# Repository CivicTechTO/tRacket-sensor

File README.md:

# tRacket: Community-Driven Urban Noise Monitoring

This repository contains all source code and hardware design files for the [tRacket](https://tracket.info/) noise sensor.

## Overview

Environmental noise, especially in urban settings, is a [known public health concern](https://www.toronto.ca/wp-content/uploads/2017/11/8f98-tph-How-Loud-is-Too-Loud-Health-Impacts-Environmental-Noise.pdf):

> The growing body of evidence indicates that exposure to excessive environmental
noise does not only impact quality of life and cause hearing loss but also has other health impacts, such as cardiovascular effects, cognitive impacts, sleep disturbance and mental health effects.

The tRacket noise sensor continuous monitors ambient sound levels (in [decibels](https://en.wikipedia.org/wiki/Decibel), dBA) and sends these measurements to an [online dashboard](https://dashboard.tracket.info/locations) ([also on GitHub](https://github.com/CivicTechTO/tRacket-dashboard)). Our goal is to help local communities better understand the sound levels and extreme noise events that they experience day to day.

The project has been started and is maintained by volunteers from the [CivicTech Toronto](http://www.civictech.ca) community.

## Privacy

We followed Privacy by Design principles in setting up the data collection. 

1. The sound meter devices are deployed on private properties in residential areas at different locations in the city. We are **not publishing exact device locations**. 
2. The devices **do not record sound** only sound levels in A-weighted decibel levels (dBA)(https://en.wikipedia.org/wiki/Decibel). 
3. We calculate minimum and maximum sound levels at 5 minute intervals on the device and **only broadcast these aggregate values** (along wiht the device ID) to a database.

## Source Code

The [noisemeter-device](/noisemeter-device) folder contains the device's source code, which is written in C++ and can be built using [PlatformIO](https://platformio.org/). Build instructions are available [in the online documentation](https://civictechto.github.io/tRacket-sensor/md_noisemeter_device_BUILD.html).

The source code is released under the [GNU GPL v3 license](/noisemeter-device/LICENSE).

## Hardware Files

The [hardware](/hardware) folder contains design files and documentation for each iteration of the sensor hardware. The PCBs are designed using [KiCAD](https://www.kicad.org/).

The hardware design files are released under an [open hardware license](/hardware/pcb-rev2/LICENSE).

## For Developers

* Check out the [Issues page](https://github.com/CivicTechTO/tRacket-sensor/issues) to see current bugs and feature requests. Any contributions are welcome!
* Online documentation of the firmware [is available here](https://civictechto.github.io/tRacket-sensor/).

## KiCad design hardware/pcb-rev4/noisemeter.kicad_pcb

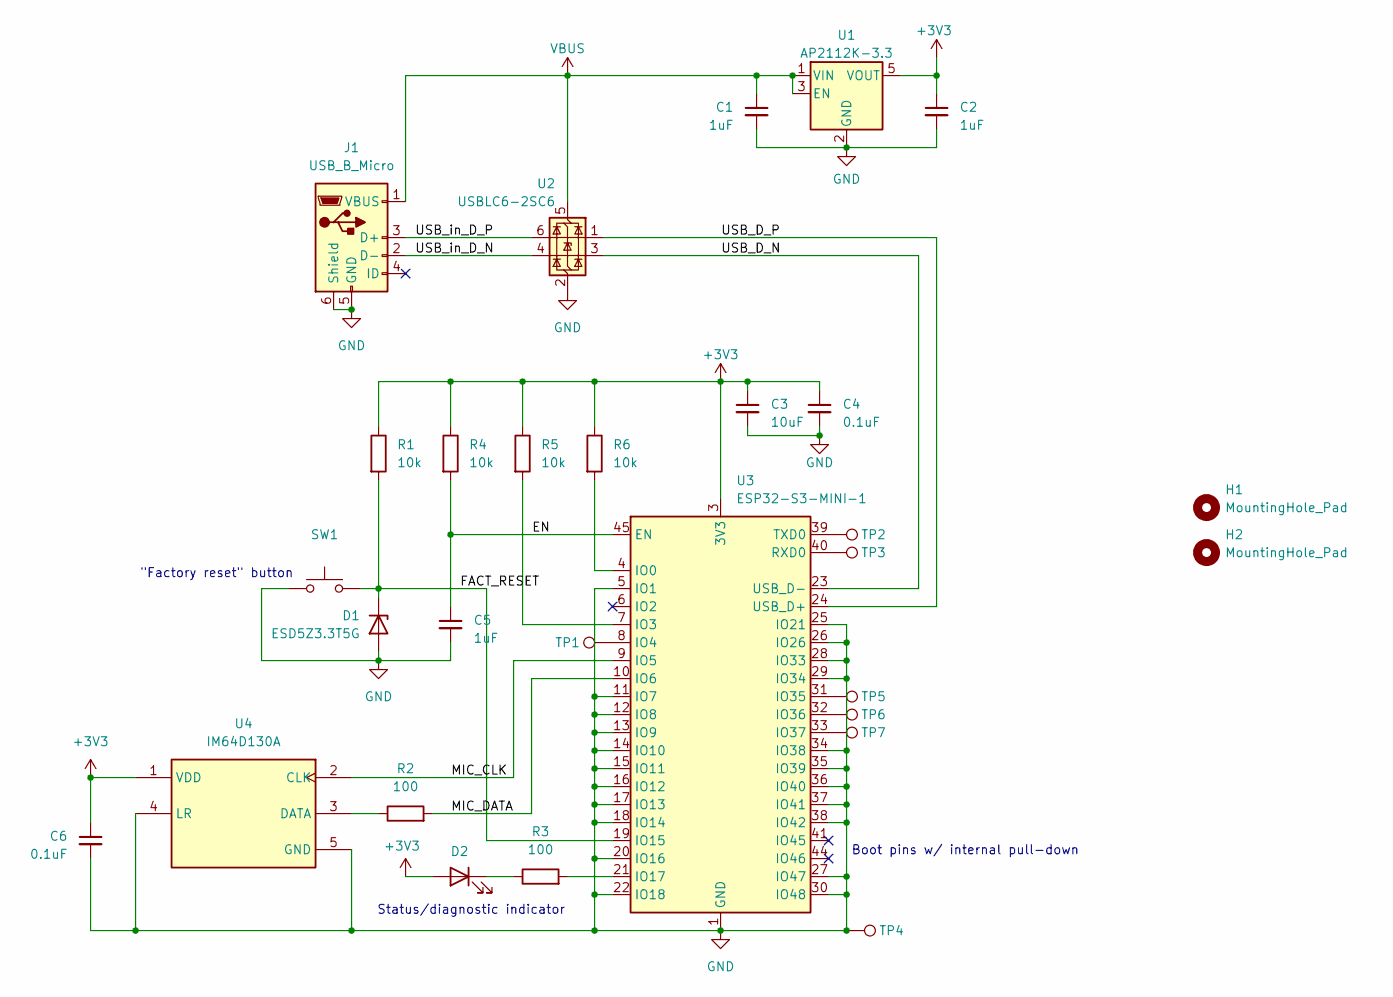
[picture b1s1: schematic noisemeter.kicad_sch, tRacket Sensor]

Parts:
C1, C2, C5: 1uF; C_0603_1608Metric; Part Number CC0603KRX7R7BB105
C3: 10uF; C_0805_2012Metric; Part Number CL21A106KOQNNNE
C4, C6: 0.1uF; C_0603_1608Metric; Part Number CC0603KRX7R6BB104
D1: ESD5Z3.3T5G; D_0603_1608Metric; Part Number ESD5Z3.3T5G
D2: LED; LED_0603_1608Metric; Part Number APT1608LVBC/D
H1, H2: MountingHole_Pad; MountingHole_2.5mm
J1: USB_B_Micro; USB_Micro-B_Molex_47346-0001; Part Number 0473460001
R1, R4, R5, R6: 10k; R_0603_1608Metric
R2, R3: 100; R_0603_1608Metric
SW1: SW_Push; SW_SPST_EVQP7C; Part Number EVQ-P7C01P
TP1, TP2, TP3, TP4, TP5, TP6, TP7: TestPoint; TestPoint_Pad_D1.0mm
U1: AP2112K-3.3; SOT-23-5; Part Number AP2112K-3.3TRG1
U2: USBLC6-2SC6; SOT-23-6; Part Number USBLC6-2SC6
U3: ESP32-S3-MINI-1; ESP32-S2-MINI-1; Part Number ESP32-S3-MINI-1-N8
U4: IM64D130A; IFX-PG-TLGA-5-6-V; Part Number IM64D130AXTMA1

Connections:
+3V3: C2.1, C3.1, C4.1, C6.1, D2.2 (A), R1.1, R4.1, R5.1, R6.1, U1.5 (VOUT), U3.3 (3V3), U4.1 (VDD)
/EN: C5.1, R4.2, U3.45 (EN)
/FACT_RESET: D1.1 (K), R1.2, SW1.1, U3.19 (IO15)
/MIC_CLK: U3.9 (IO5), U4.2 (CLK)
/MIC_DATA: R2.2, U3.10 (IO6)
/USB_D_N: U2.3 (I/O2), U3.23 (USB_D-)
/USB_D_P: U2.1 (I/O1), U3.24 (USB_D+)
/USB_in_D_N: J1.2 (D-), U2.4 (I/O2)
/USB_in_D_P: J1.3 (D+), U2.6 (I/O1)
GND: C1.2, C2.2, C3.2, C4.2, C5.2, C6.2, D1.2 (A), J1.5 (GND), J1.6 (Shield), SW1.2, TP4.1, U1.2 (GND), U2.2 (GND), U3.1 (GND), U3.2 (GND), U3.5 (IO1), U3.11 (IO7), U3.12 (IO8), U3.13 (IO9), U3.14 (IO10), U3.15 (IO11), U3.16 (IO12), U3.17 (IO13), U3.18 (IO14), U3.20 (IO16), U3.22 (IO18), U3.25 (IO21), U3.26 (IO26), U3.27 (IO47), U3.28 (IO33), U3.29 (IO34), U3.30 (IO48), U3.34 (IO38), U3.35 (IO39), U3.36 (IO40), U3.37 (IO41), U3.38 (IO42), U3.42 (GND), U3.43 (GND), U3.46 (GND), U3.47 (GND), U3.48 (GND), U3.49 (GND), U3.50 (GND), U3.51 (GND), U3.52 (GND), U3.53 (GND), U3.54 (GND), U3.55 (GND), U3.56 (GND), U3.57 (GND), U3.58 (GND), U3.59 (GND), U3.60 (GND), U3.61 (GND), U3.62 (GND), U3.63 (GND), U3.64 (GND), U3.65 (GND), U4.4 (LR), U4.5 (GND)
unnamed: D2.1 (K), R3.1
unnamed: R6.2, U3.4 (IO0)
unnamed: R5.2, U3.7 (IO3)
unnamed: TP1.1, U3.8 (IO4)
unnamed: R3.2, U3.21 (IO17)
unnamed: TP5.1, U3.31 (IO35)
unnamed: TP6.1, U3.32 (IO36)
unnamed: TP7.1, U3.33 (IO37)
unnamed: TP3.1, U3.40 (RXD0)
unnamed: TP2.1, U3.39 (TXD0)
unnamed: R2.1, U4.3 (DATA)
VBUS: C1.1, J1.1 (VBUS), U1.1 (VIN), U1.3 (EN), U2.5 (VBUS)

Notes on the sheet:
Status/diagnostic indicator
Boot pins w/ internal pull-down
"Factory reset" button

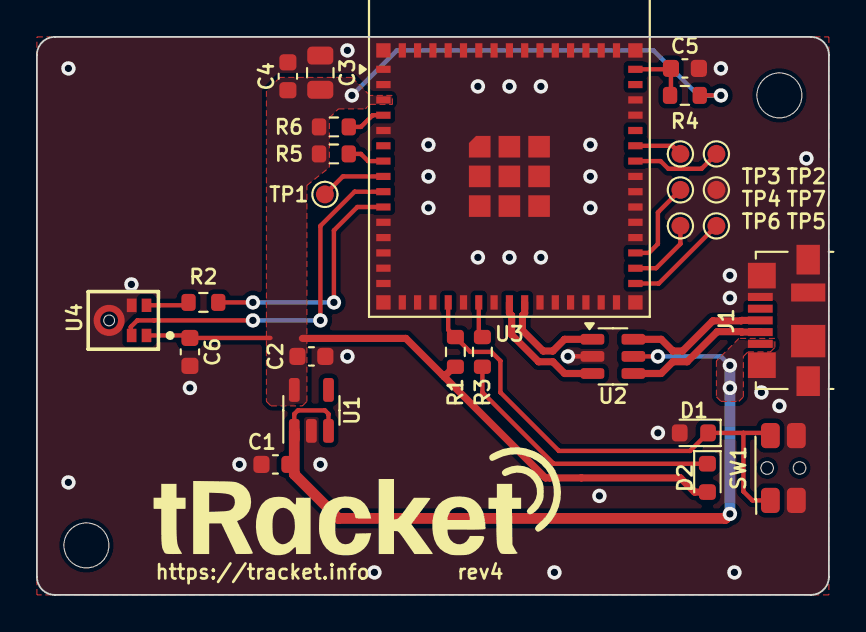
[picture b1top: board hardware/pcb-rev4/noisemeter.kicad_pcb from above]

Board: 2 copper layers, 44.0 x 31.0 mm, 29 parts (0 on the bottom side), 22 nets.

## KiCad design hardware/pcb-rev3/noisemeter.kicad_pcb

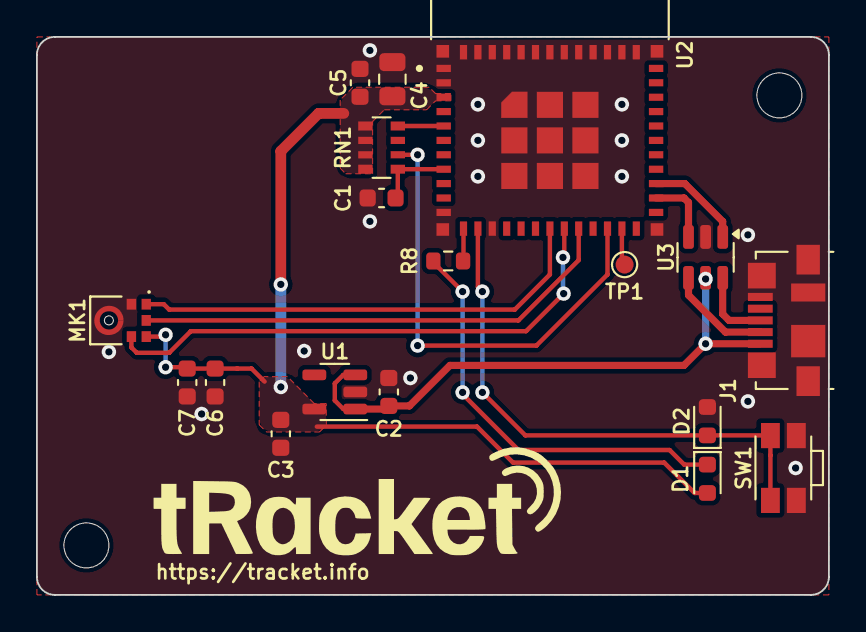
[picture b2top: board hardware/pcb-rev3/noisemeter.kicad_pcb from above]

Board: 2 copper layers, 44.0 x 31.0 mm, 20 parts (0 on the bottom side), 17 nets.

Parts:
C1, C2, C3: 1uF; C_0603_1608Metric
C4: 10uF; C_0805_2012Metric
C5, C6: 0.1uF; C_0603_1608Metric
C7: 200pF; C_0603_1608Metric
D1: LED; LED_0603_1608Metric
D2: ESD5Z3.3T5G; D_0603_1608Metric
H1, H2: MountingHole_Pad; MountingHole_2.5mm
J1: USB_B_Micro; USB_Micro-B_Molex_47346-0001
MK1: SPH0645LM4H-B; MIC_SPH0645LM4H-B
R8: 51; R_0603_1608Metric
RN1: 10k; R_Array_Convex_4x0603
SW1: SW_Push; SW_SPST_EVQP7A
TP1: TestPoint; TestPoint_Pad_D1.0mm
U1: AP2112K-3.3; SOT-23-5
U2: ESP32-C3-MINI-1-N4; XCVR_ESP32-C3-MINI-1-N4
U3: USBLC6-2SC6; SOT-23-6

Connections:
+3V3: C3.1, C4.1, C5.1, C6.1, C7.1, D1.2 (A), MK1.5 (VDD), RN1.5 (R4.2), RN1.6 (R3.2), RN1.7 (R2.2), RN1.8 (R1.2), U1.5 (VOUT), U2.3 (3V3)
FACT_RESET: D2.1 (K), SW1.1, U2.13 (IO1)
GND: C1.2, C2.2, C3.2, C4.2, C5.2, C6.2, C7.2, D2.2 (A), J1.5 (GND), J1.6 (Shield), MK1.2 (SELECT), MK1.3 (GND), SW1.2, U1.2 (GND), U2.1 (GND), U2.2 (GND), U2.11 (GND), U2.14 (GND), U2.36 (GND), U2.37 (GND), U2.38 (GND), U2.39 (GND), U2.40 (GND), U2.41 (GND), U2.42 (GND), U2.43 (GND), U2.44 (GND), U2.45 (GND), U2.46 (GND), U2.47 (GND), U2.48 (GND), U2.49_1 (GND), U2.49_2 (GND), U2.49_3 (GND), U2.49_4 (GND), U2.49_5 (GND), U2.49_6 (GND), U2.49_7 (GND), U2.49_8 (GND), U2.49_9 (GND), U2.50 (GND), U2.51 (GND), U2.52 (GND), U2.53 (GND), U3.2 (GND)
IO2: RN1.4 (R4.1), U2.5 (IO2)
IO8: RN1.2 (R2.1), U2.22 (IO8)
MIC_BCLK: MK1.4 (BCLK), U2.19 (IO5)
MIC_DATA_OUT: MK1.6 (DATA_OUT), U2.20 (IO6)
MIC_WS: MK1.1 (WS), U2.18 (IO4)
unnamed: D1.1 (K), R8.2
unnamed: C1.1, RN1.1 (R1.1), U2.8 (EN)
unnamed: TP1.1, U2.23 (IO9)
STAT_LED: R8.1, U2.12 (IO0)
USB_D_N: U2.26 (IO18), U3.3 (I/O2)
USB_D_P: U2.27 (IO19), U3.1 (I/O1)
USB_in_D_N: J1.2 (D-), U3.4 (I/O2)
USB_in_D_P: J1.3 (D+), U3.6 (I/O1)
VBUS: C2.1, J1.1 (VBUS), U1.1 (VIN), U1.3 (EN), U3.5 (VBUS)

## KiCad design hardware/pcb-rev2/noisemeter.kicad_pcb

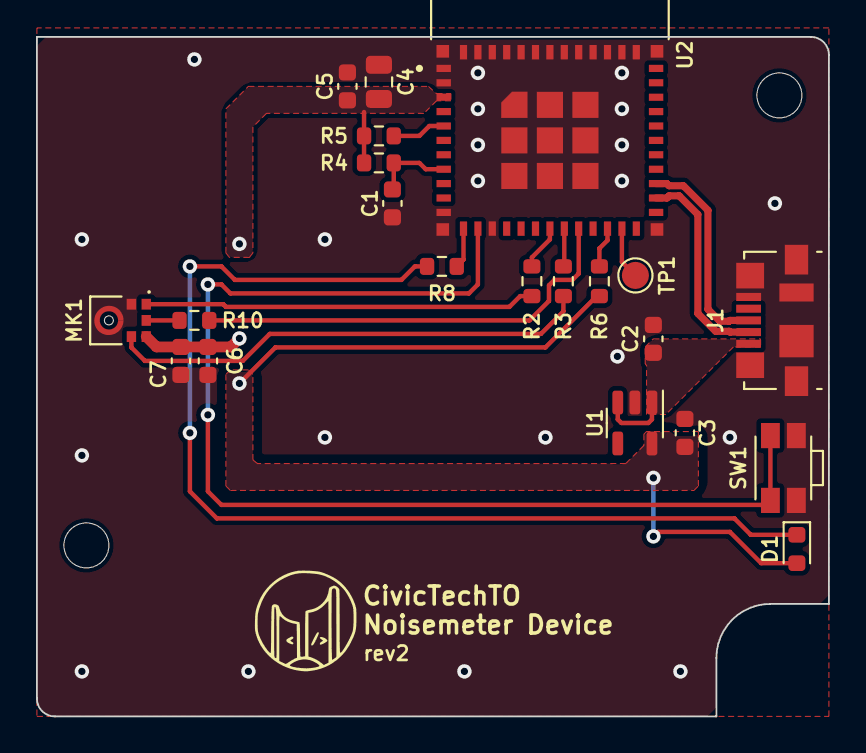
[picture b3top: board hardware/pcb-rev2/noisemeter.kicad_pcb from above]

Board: 2 copper layers, 44.0 x 37.8 mm, 23 parts (0 on the bottom side), 18 nets.

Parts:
C1, C2, C3: 1U; C_0603_1608Metric
C4: 10U; C_0805_2012Metric
C5, C6: 0.1U; C_0603_1608Metric
C7: 200P; C_0603_1608Metric
D1: LED; LED_0603_1608Metric
H1, H2: MountingHole_Pad; MountingHole_2.5mm
J1: USB_B_Micro; USB_Micro-B_Molex_47346-0001
MK1: SPH0645LM4H-B; MIC_SPH0645LM4H-B
R2, R3, R8, R10: 51; R_0603_1608Metric
R4, R5, R6: 10K; R_0603_1608Metric
SW1: SW_Push; SW_SPST_EVQP7A
TP1: TestPoint; TestPoint_Pad_D1.5mm
U1: AP2112K-3.3; SOT-23-5
U2: ESP32-C3-MINI-1-N4; XCVR_ESP32-C3-MINI-1-N4

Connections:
+3V3: C3.1, C4.1, C5.1, C6.1, C7.1, D1.2 (A), MK1.5 (VDD), R4.2, R5.2, R6.2, U1.5 (VOUT), U2.3 (3V3)
FACT_RESET: SW1.1, U2.13 (IO1)
GND: C1.2, C2.2, C3.2, C4.2, C5.2, C6.2, C7.2, J1.5 (GND), J1.6 (Shield), MK1.2 (SELECT), MK1.3 (GND), SW1.2, U1.2 (GND), U2.1 (GND), U2.2 (GND), U2.11 (GND), U2.14 (GND), U2.36 (GND), U2.37 (GND), U2.38 (GND), U2.39 (GND), U2.40 (GND), U2.41 (GND), U2.42 (GND), U2.43 (GND), U2.44 (GND), U2.45 (GND), U2.46 (GND), U2.47 (GND), U2.48 (GND), U2.49_1 (GND), U2.49_2 (GND), U2.49_3 (GND), U2.49_4 (GND), U2.49_5 (GND), U2.49_6 (GND), U2.49_7 (GND), U2.49_8 (GND), U2.49_9 (GND), U2.50 (GND), U2.51 (GND), U2.52 (GND), U2.53 (GND)
IO2: R5.1, U2.5 (IO2)
IO8: R6.1, U2.22 (IO8)
MIC_BCLK: MK1.4 (BCLK), R3.1
MIC_DATA_OUT: R10.2, U2.20 (IO6)
MIC_WS: MK1.1 (WS), R2.1
unnamed: D1.1 (K), R8.2
unnamed: MK1.6 (DATA_OUT), R10.1
unnamed: C1.1, R4.1, U2.8 (EN)
unnamed: R2.2, U2.18 (IO4)
unnamed: R3.2, U2.19 (IO5)
unnamed: TP1.1, U2.23 (IO9)
STAT_LED: R8.1, U2.12 (IO0)
USB_D_N: J1.2 (D-), U2.26 (IO18)
USB_D_P: J1.3 (D+), U2.27 (IO19)
VBUS: C2.1, J1.1 (VBUS), U1.1 (VIN), U1.3 (EN)

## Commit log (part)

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2023-12-31 Add hardware folders
2023-12-31 Add Wemos D1 Reference Repos
2023-12-31 Add more Wemos D1 Code
2023-12-31 Add more reference code
2023-12-31 Add .gitignore
2023-12-31 Add Raspberry Pi code
2023-12-31 Add creds erasure to Wifi Creds manager
2023-12-31 Add ESP32 pinout & connections table
2023-12-31 Add pinout for Wemos D1 Mini
2023-12-31 Add v1 for esp32
2023-12-31 Add HTTPS example for ESP32
2023-12-31 Settings
2024-01-01 Add HTTPS upload to ESP32 v1
2024-01-01 Add mic reading functionality to ESP32 v1
2024-01-01 Add notes, tweak debug
2024-01-01 Add info to readme
2024-01-01 Fix formatting on Readme
2024-01-01 Add more pin info for ESP32 Readme
2024-01-02 Modify gitignore, add certs.py
2024-01-02 Update ESP v1 notes
2024-01-02 Fix typos
2024-01-03 Fix upload data shape
2024-01-11 add kicad files
2024-01-11 Add debug mode constant to disable upload
2024-01-11 add hardware license
2024-01-19 initial port to pcb
2024-01-19 add images for wiki
2024-01-21 status LEDs; SERIAL definition
2024-01-22 remove WIFI_DISABLED
2024-01-24 move bringup to esp32c3 folder
2024-01-24 bring back esp32 implementation
2024-01-27 Add Captive Portal reference project
2024-01-27 OTA proof of concept
2024-01-28 encryption proof-of-concept
2024-01-29 Remove 3dB boost from MIC_OFFSET_DB
2024-01-30 schematic/layout draft
2024-02-04 redesign for 1551SFL case
2024-02-04 remove esp8266 and raspi sources
2024-02-04 add platformio support
2024-02-04 restore pcb-rev1 hw files
2024-02-05 certs.py: remove "RUNNING" message
    Allows for collecting output directly to the header file.
2024-02-05 add rev2 files
2024-02-07 finalize rev2 design
2024-02-09 platformio.ini: downgrade espressif32 to v6.1.0
    https://github.com/platformio/platform-espressif32/issues/1285
2024-02-13 Add UUID generation functionality
2024-02-16 final edits and bom changes
2024-02-16 rename pcb-rev1 to esp32-pcb
    pcb rev2 is identical, let's use a common name
2024-02-16 Try github actions
2024-02-16 actions: switch to node 20
2024-02-16 actions: proper fix for node deprecation
2024-02-16 Update main.yml again
    Create certs.h and secret.h
2024-02-16 Update main.yml: remove extra step
    I'm trying. This better be it.
2024-02-16 Update README.md
    Forgot to remove "release candidate" after the source merge.
2024-02-16 Update README.md
    Fix links and other edits
2024-02-17 modularize access point code
2024-02-18 comment out UUID code
    Overwrites checksum causing WiFi creds check to always fail
2024-02-18 create Storage module
2024-02-24 enable more compiler warnings; some c++ changes
2024-02-24 move config.h include to board.h
    fixes arduino builds
2024-02-24 remove isCredsResetPressed
2024-02-24 add timestamp class
2024-03-05 timestamp upload packets
2024-03-05 add DataPacket
2024-03-05 batch uploads in case WiFi is lost
2024-03-06 simplified packet processing; timestamp replaces millis
2024-03-08 captive portal support for AccessPoint
2024-03-09 remove todo comment
2024-03-11 add pcb-rev2 image
2024-03-15 fetch ota updates from github
2024-03-16 don't dump credentials to serial
2024-03-18 add OTAUpdate; use webcomand endpoints
2024-03-19 check for ota every 24 hours
2024-03-24 discard empty packets; set limit to stored packets
2024-03-24 only check for OTA when there's WiFi
2024-03-24 only enable OTA for PCBs
2024-03-26 fixed UUID for device ID based on MAC
2024-03-26 add wifi timeout and fix empty ssid check
2024-03-26 blink led during access point
2024-03-26 fix credentials erase
2024-03-26 bump to 0.0.3
2024-04-01 fix wifi connected typo
    Really should have caught this before pushing, ugh.
2024-04-01 round decibel readings to integers
2024-04-01 fix debug print order
2024-04-02 Blinker class for WiFi indications
2024-04-03 wip: HMAC for key generation
2024-04-03 encryption with protected hmac key
2024-04-03 disable encryption for breadboard
2024-04-04 add efuse note to readme
2024-04-04 update gitignore
2024-04-04 get splmeter to compile
2024-04-04 mic variable cleanup
2024-04-11 license source code under gplv3
2024-04-11 document source code and add Doxyfile
2024-04-11 support doxygen from root directory
2024-04-11 add doc gen action
2024-04-11 Update Doxyfile
2024-04-11 Deploying to gh-pages from @ CivicTechTO/proj-noisemeter-device@6feb23a329cf4f042d48645b363db8dbdb118915 🚀
2024-04-11 Initial gh-pages commit
2024-04-13 no need to allocate WiFiClientSecure outside of uploadData
2024-04-13 Deploying to gh-pages from @ CivicTechTO/proj-noisemeter-device@ea43e63d75c4e3a808215568bf41ac164a7e7193 🚀
2024-04-13 type cleanup
2024-04-13 member cleanup and replace defines with constexpr
2024-04-13 document splmeter
2024-04-13 Deploying to gh-pages from @ CivicTechTO/proj-noisemeter-device@aaf98cc5e91aab59cf2ce8d26d5f8eb453468cb7 🚀
2024-04-13 bump version
2024-04-13 Deploying to gh-pages from @ CivicTechTO/proj-noisemeter-device@a869d3741eccc741155e17f27c845a50918fb4d7 🚀
2024-05-09 fix for encrypted credentials storage
    Copy entire memory allocated to string since encryption can create false null terminators
2024-05-11 refactor storage encryption
2024-05-11 Deploying to gh-pages from @ CivicTechTO/proj-noisemeter-device@b626f4e640a8e9b18841709e72e64c52c7438ac9 🚀
2024-05-11 setup form: email field, rejection path; store api token
2024-05-12 tested new API; clean up .ino
2024-05-12 api.h documentation
2024-05-17 change Unauthorized to Non-authorized
2024-05-17 keep sound readings on single line
2024-05-17 use tracket.info api base
2024-05-18 timestamp: include UTC suffix (+00:00)
2024-05-18 api refactoring; send boottime/version with first packet
2024-05-19 register device while in AP mode
2024-05-19 timeout tweaks; poweroff on no AP connection
2024-05-21 wip: ota signing
2024-05-21 fix secure build instruction
2024-05-23 fix signed ota; dummy key for Action
2024-05-23 change wifi connection timeouts
2024-05-23 only register if email is provided
2024-05-28 access point: do not require passkey
    For open networks & match previous form behavior
2024-05-28 Deploying to gh-pages from @ CivicTechTO/proj-noisemeter-device@e9566d70d562b4bb10cff9ab7d0142801a84bf13 🚀
2024-05-28 remove arduino ide support
2024-07-02 new web form
2024-07-02 tracket ssid/passkey
2024-07-02 misc fixes
    Keep extra storage entry so checksum is not ruined; clear API token if re-registering; blink faster for multi-packet send
2024-07-02 Deploying to gh-pages from @ CivicTechTO/proj-noisemeter-device@fae14a7ec652527ee97f8816672cd29705a11edb 🚀
2024-07-06 api: use POST to encrypt payloads
2024-07-11 Basic loading screen for access point UI
2024-07-19 Switched back to println for console readings.
2024-07-19 uncomment registration api call
2024-07-20 adjust input field to not auto-capitalize
2024-07-20 increase process stack for registration
2024-07-20 fix token validity checks
2024-07-22 fix HR_TO_SEC and DAY_TO_SEC
    silly mistake
2024-07-22 Deploying to gh-pages from @ CivicTechTO/proj-noisemeter-device@6768b300f15f4001169a43619c436f5f2f365302 🚀
2024-08-05 use GET for software/latest
2024-08-08 move returns out of API_VERBOSE
2024-09-08 remove .vscode
2024-09-08 Deploying to gh-pages from @ CivicTechTO/proj-noisemeter-device@a3c98c4c7f5303cea7540223178521ee58f1e3b7 🚀
2024-09-08 fix version
2024-09-22 bump version for ota test
2024-09-22 add draft rev3 files
2024-09-22 minor schematic fixes
2024-10-08 cleaning up layout
2024-10-19 remove unused tracket logo
2024-10-19 add pcb render
2024-10-19 fix readme links
2024-10-19 ssid dropdown proof-of-concept
2024-10-19 setup form tweaks; use lock emoji for ssids
2024-10-27 pcb-rev3: add freecad file
2024-10-27 Create ota-release.yml
    Trying to automate signed OTA update generation.
2024-10-29 add initial bringup script
2024-10-29 only sign firmware when necessary
2024-10-29 oops, fix platformio-only
2024-10-29 update readmes
2024-11-02 ota-release: remove config.h
2024-11-02 platformio.ini: fix whitespace
2024-11-02 Deploying to gh-pages from @ CivicTechTO/tRacket-sensor@6319bfd0520b4f36257c44eecaa26a237d681052 🚀
2025-01-02 access point: add manual entry page
2025-01-18 Deploying to gh-pages from @ CivicTechTO/tRacket-sensor@1f0944e525b79f7db3b33f1edaab4604d92496a2 🚀
2025-01-18 force sensor reading to be non-negative
    very lazy fix
2025-02-08 Update README.md
    fix incorrect url
2025-03-29 use X-Tracket-Device header
2025-03-29 use measurements endpoint for bulk upload
2025-03-29 main.yml: update actions/cache
2025-03-30 multithreaded mic sampling
2025-03-30 start mic task immediately
2025-10-26 update platform version
2025-10-26 esp32s3 and pdm mic proof-of-concept
2025-12-06 add rev4 hardware files
2025-12-14 update ci python version
2025-12-14 remove ci build for esp32-breadboard
2026-01-10 finalize rev4 hardware
2026-01-17 firmware working on rev4 boards
2026-06-12 refactor: keep support for earlier revs
    Changed board definitions; ported older revs to latest I2S library; force older revs to only accept pre-v0.4 updates
2026-06-12 update env for github actions
2026-06-12 Deploying to gh-pages from @ CivicTechTO/tRacket-sensor@b499f8a650c620d377633710515e9ab715179380 🚀
2026-06-29 data point every minute; ota separation for rev4; access point fixes
    New access point passkey!
2026-06-30 Build both OTA releases

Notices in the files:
hardware/pcb-rev2/noisemeter.kicad_pcb:
Released under the CERN Open Hardware License Version 2 - Strongly Reciprocal
